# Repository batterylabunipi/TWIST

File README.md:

# TWIST
TWIST is an open framework for Li-ion cell characterization based on Python and Raspberry Pi

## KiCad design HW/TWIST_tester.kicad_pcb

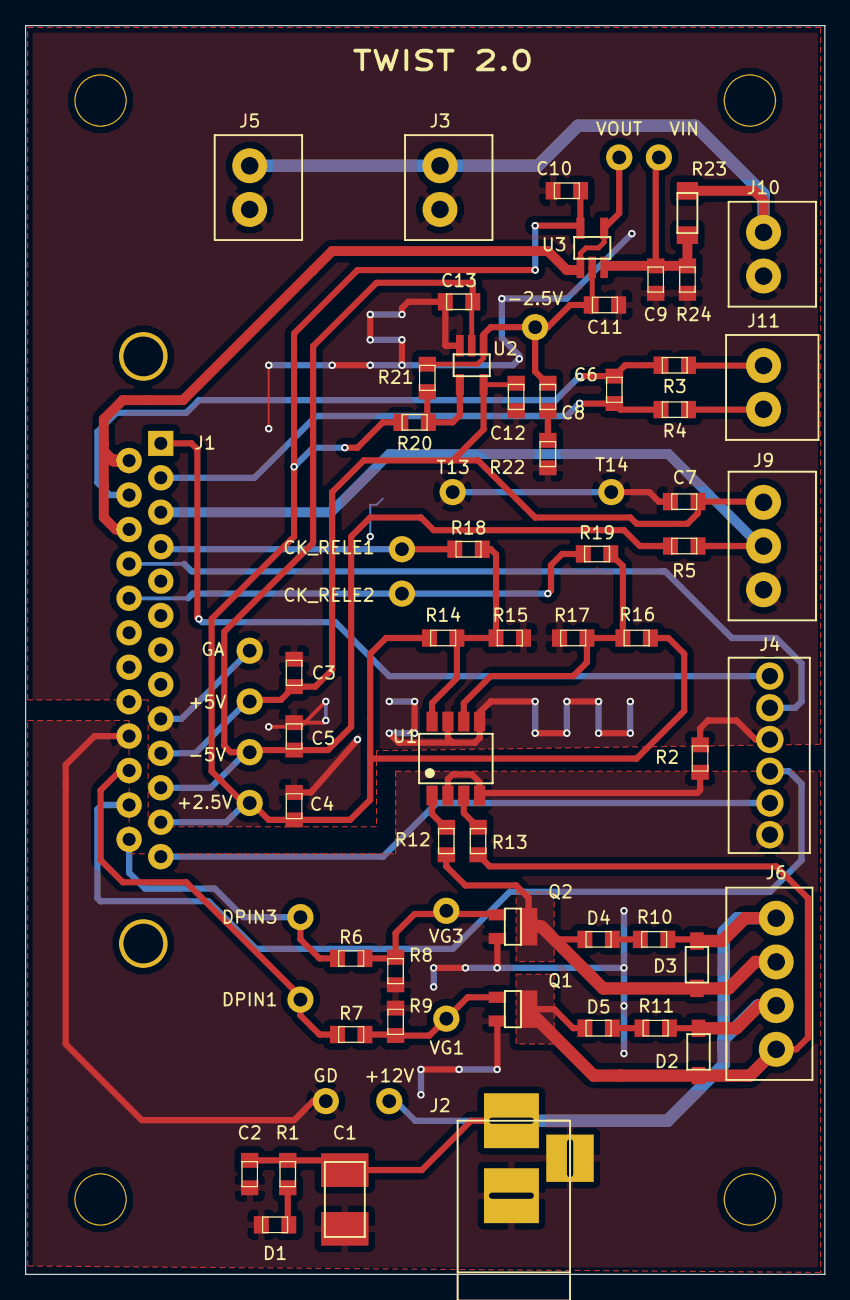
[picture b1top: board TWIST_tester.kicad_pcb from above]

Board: 2 copper layers, 64.0 x 100.0 mm, 73 parts (0 on the bottom side), 36 nets.

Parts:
+2.5V, +5V, +12V: TestPoint; TSTPOINT
-2.5V, -5V: TestPoint; TSTPOINT
C1: 100uF; C_2312
C2, C3, C4, C5, C10, C11, C12, C13: 100nF; 0805
C6: 100u; 0805
C7: 100nf; 0805
C8: 1u; 0805
C9: 1uF; 0805
CK_RELE1, CK_RELE2: TestPoint; TSTPOINT
D1: LED_G; 0805
D2, D3: MBR0520L; SOD-123
D4: LED_Y; 0805
D5: LED_R; 0805
DPIN1, DPIN3: TestPoint; TSTPOINT
GA: TestPoint; TSTPOINT
GD: TestPoint; TSTPOINT
J1: DB25_MALE; DB25MC
J2: ALIM_JACK; conn_alim
J3, J5, J10: morsett_1x02_MALE; morsett_1x02
J4: CONN_01X06; morsett_1x06_CB
J6: CONN_01X04_MALE; morsett_1x04
J9: morsett_1x03_MALE; morsett_1x03
J11: morsett_1x02_MALE; morsett_1x02_G
Q1, Q2: DMG3420U; SOT-23-3-POT
R1, R3, R4, R10, R11: 1k; 0805
R2, R14, R16: 100k; 0805
R5, R8, R9: 100K; 0805
R6, R7: 10K; 0805
R12, R13: 1K; 0805
R15, R17: 66.5k; 0805
R18, R19: 0; 0805
R20, R21: 1M; 0805
R22: 2k; 0805
R23: 990K; R_1206
R24: 330K; 0805
T13, T14: TestPoint; TSTPOINT
U1: VOD205T; 8-SOIC
U2: LT6003; SOT-23-5
U3: ADA4051; SOT-23-5
VG1, VG3: TestPoint; TSTPOINT
VIN: TestPoint; TSTPOINT
VOUT: TestPoint; TSTPOINT

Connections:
+2V5: +2.5V.1, C4.1, C10.1, J1.12, R14.1, R16.1, R20.2, U3.5
+5V: +5V.1, C3.1, C7.1, C12.1, J1.10, J9.1, U2.5
+12V: +12V.1, C1.1, C2.1, D2.1, D3.1, J2.1, J6.2, J6.4, R1.1, R10.1, R11.1
-5V: -5V.1, C5.1, C13.2, J1.11, R5.2, U2.2
/CH2: J1.1, J4.6
/CH7: J1.17, J4.5
/CHK_RE1: CK_RELE1.1, J1.4, R18.1
/CHK_RE2: CK_RELE2.1, J1.18, R19.1
/COIL1-: D3.2, D4.1, J6.3, Q2.3, R12.2
/COIL2-: D2.2, D5.1, J6.1, Q1.3, R13.2
/DPIN1: DPIN1.1, J1.23, R7.1
/DPIN2: J1.24, J4.3
/DPIN3: DPIN3.1, J1.25, R6.1
/DPIN4: J1.13, J4.2
/SHUNT+: C6.1, J1.15, R3.2
/SHUNT-: C6.2, J1.2, R4.2
/TEMP: J1.3, J9.2, R5.1
/VB+: J3.1, J5.1, J10.1, R23.1
/VBATT+: J1.14, J1.16, U3.1, U3.4, VOUT.1
GNDA: C3.2, C4.2, C5.2, C7.2, C9.2, C10.2, C11.2, C12.2, C13.1, GA.1, J1.9, J3.2, J4.4, J5.2, J9.3, J10.2, R2.2, R15.2, R17.2, R22.2, R24.2, T13.1, T14.1, U1.5, U1.7, U2.3
GNDD: C1.2, C2.2, D1.1, GD.1, J1.22, J2.2, J2.3, J4.1, Q1.2, Q2.2, R2.1, R8.2, R9.2, U1.2, U1.4
unnamed: C8.2, R22.1
unnamed: C9.1, R23.2, R24.1, U3.3, VIN.1
unnamed: -2.5V.1, C8.1, C11.1, R21.1, U2.1, U3.2
unnamed: D1.2, R1.2
unnamed: D4.2, R10.2
unnamed: D5.2, R11.2
unnamed: J11.1, R3.1
unnamed: J11.2, R4.1
unnamed: Q1.1, R7.2, R9.1, VG1.1
unnamed: Q2.1, R6.2, R8.1, VG3.1
unnamed: R12.1, U1.1
unnamed: R13.1, U1.3
unnamed: R14.2, R15.1, R18.2, U1.8
unnamed: R16.2, R17.1, R19.2, U1.6
unnamed: R20.1, R21.2, U2.4

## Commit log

2018-10-03 Rename LICENSE to SW/LICENSE
